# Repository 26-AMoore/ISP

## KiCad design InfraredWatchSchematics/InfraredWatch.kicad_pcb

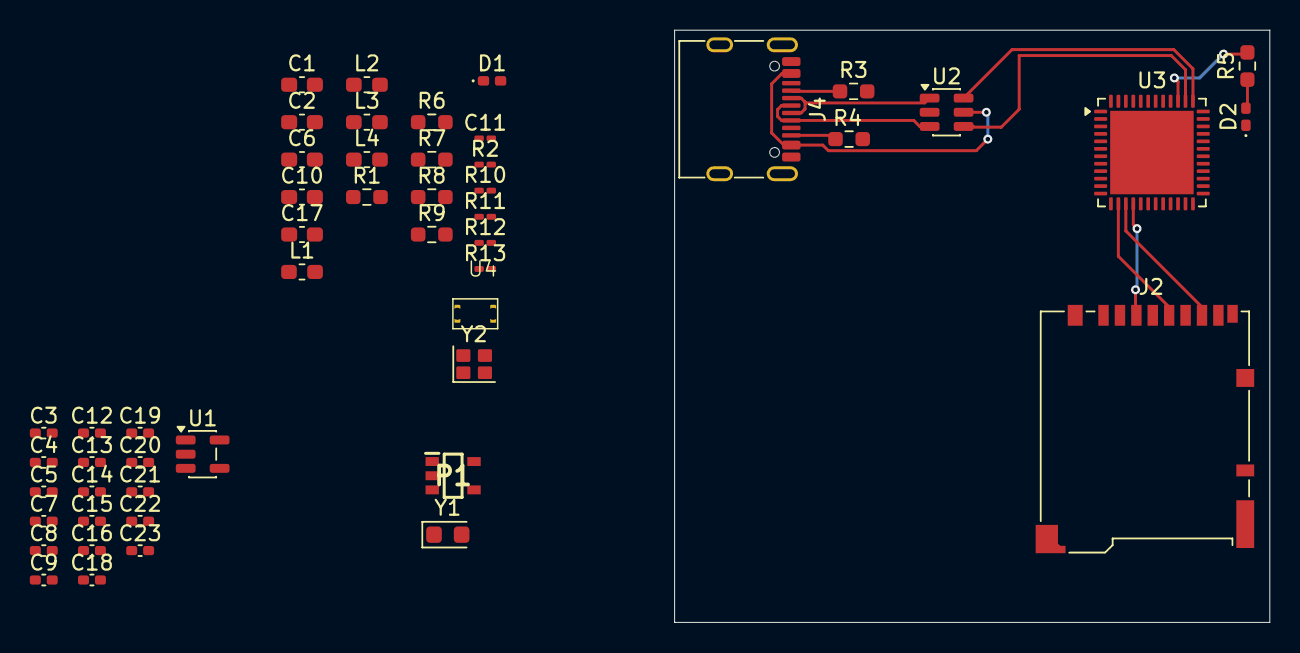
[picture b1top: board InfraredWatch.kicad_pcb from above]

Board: 4 copper layers, 39.9 x 39.7 mm, 51 parts (0 on the bottom side), 32 nets.

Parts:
C1, C2, C6, C10, C17: 4.7uF; C_0603_1608Metric_Pad1.08x0.95mm_HandSolder
C3, C4, C5, C7, C8, C9, C12, C13, C20, C21, C22, C23: 100nF; C_0402_1005Metric_Pad0.74x0.62mm_HandSolder
C11: 10uF; C_0201_0603Metric_Pad0.64x0.40mm_HandSolder
C14: 22uF; C_0402_1005Metric_Pad0.74x0.62mm_HandSolder
C15, C16: C; C_0402_1005Metric_Pad0.74x0.62mm_HandSolder
C18: 0.8pF; C_0402_1005Metric_Pad0.74x0.62mm_HandSolder
C19: 0.3pF; C_0402_1005Metric_Pad0.74x0.62mm_HandSolder
D1: CHARGE_INDICATOR; LED_0402_1005Metric_Pad0.77x0.64mm_HandSolder
D2: LED; LED_0402_1005Metric_Pad0.77x0.64mm_HandSolder
J2: Micro_SD_Card_Det2; microSD_HC_Hirose_DM3BT-DSF-PEJS
J4: USB_C_Receptacle_USB2.0_16P; USB_C_Receptacle_G-Switch_GT-USB-7010ASV
L1, L2: 10uH; L_0603_1608Metric_Pad1.05x0.95mm_HandSolder
L3: 10nH; L_0603_1608Metric_Pad1.05x0.95mm_HandSolder
L4: 2.7nH; L_0603_1608Metric_Pad1.05x0.95mm_HandSolder
P1: XC9265A331MR-G
R1: 2k; R_0603_1608Metric_Pad0.98x0.95mm_HandSolder
R2: 470; R_0201_0603Metric_Pad0.64x0.40mm_HandSolder
R3, R4, R6, R7, R8, R9: 5.1k; R_0603_1608Metric_Pad0.98x0.95mm_HandSolder
R5: R; R_0603_1608Metric_Pad0.98x0.95mm_HandSolder
R10, R11, R12, R13: 100; R_0201_0603Metric_Pad0.64x0.40mm_HandSolder
U1: MCP73831-5-OT; SOT-23-5
U2: USBLC6-2SC6; SOT-23-6
U3: STM32WB55CGU6; QFN-48-1EP_7x7mm_P0.5mm_EP5.6x5.6mm
U4: A1001312
Y1: 32.768kHz; Crystal_SMD_2012-2Pin_2.0x1.2mm_HandSoldering
Y2: 32MHz; Crystal_SMD_SeikoEpson_FA128-4Pin_2.0x1.6mm

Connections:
+BATT: C6.1, C11.1, P1.1 (V_IN), U1.3 (V_{BAT})
/BOOT0/Button3: C23.1, R9.1, R13.1, U3.4 (PH3)
/HSC_In: U3.25 (OSC_IN), Y2.1
/HSC_Out: U3.24 (OSC_OUT), Y2.3
/IR: R5.2, U3.39 (PA13)
/LSE_In: C16.1, U3.2 (PC14), Y1.2
/LSE_Out: C15.1, U3.3 (PC15), Y1.1
/RF: C18.1, L4.1, U3.21 (RF1)
/SD_CLK: J2.5 (CLK), U3.14 (PA5)
/SD_MISO: J2.7 (DAT0), U3.15 (PA6)
/SD_MOSI: J2.3 (CMD), U3.16 (PA7)
/SMBSFB: C17.2, L3.2, U3.31 (VFBSMPS)
/SMBSLX: L2.1, U3.33 (VLXSMPS)
/USB_D+: U2.4 (I/O2), U3.38 (PA12)
/USB_D-: U2.6 (I/O1), U3.37 (PA11)
Button0: C20.1, R6.1, R10.1, U3.9 (PA0)
Button1: C21.1, R7.1, R11.1, U3.10 (PA1)
Button2: C22.1, R8.1, R12.1, U3.11 (PA2)
CHARGE_IN: C1.1, J4.A4 (VBUS), J4.A9 (VBUS), J4.B4 (VBUS), J4.B9 (VBUS), R2.1, U1.4 (V_{DD}), U2.5 (VBUS)
GND: C1.2, C2.2, C3.2, C4.2, C5.2, C6.2, C7.2, C8.2, C9.2, C10.2, C11.2, C12.2, C13.2, C14.2, C15.2, C16.2, C17.1, C18.2, C19.2, C20.2, C21.2, C22.2, C23.2, D2.1 (K), J2.2 (DAT3/CD), J2.6 (VSS), J4.A1 (GND), J4.A12 (GND), J4.B1 (GND), J4.B12 (GND), J4.SH (SHIELD), P1.2 (GND), R1.1, R3.2, R4.2, R6.2, R7.2, R8.2, R9.2, U1.2 (V_{SS}), U2.2 (GND), U3.22 (VSSRF), U3.32 (VSSSMPS), U3.49 (VSS), U4.2 (GND), Y2.2 (G), Y2.4 (G)
unnamed: D1.2 (A), R2.2
unnamed: D1.1 (K), U1.1 (STAT)
unnamed: D2.2 (A), R5.1
unnamed: C19.1, L4.2
unnamed: J4.A5 (CC1), R3.1
unnamed: J4.B5 (CC2), R4.1
unnamed: J4.A6 (D+), J4.B6 (D+), U2.3 (I/O2)
unnamed: J4.A7 (D-), J4.B7 (D-), U2.1 (I/O1)
unnamed: L2.2, L3.1
unnamed: L1.1, P1.5 (LX)
unnamed: R1.2, U1.5 (PROG)
Power: C2.1, C3.1, C4.1, C5.1, C7.1, C8.1, C9.1, C10.1, C12.1, C13.1, C14.1, J2.4 (VDD), L1.2, P1.4 (V_OUT), U3.1 (VBAT), U3.8 (VDDA), U3.20 (VDD), U3.23 (VDDRF), U3.34 (VDDSMPS), U3.35 (VDD), U3.40 (VDDUSB), U3.48 (VDD)

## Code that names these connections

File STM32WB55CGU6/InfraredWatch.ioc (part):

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Mcu.Name=STM32WB55CCUx
Mcu.Package=UFQFPN48
Mcu.UserName=STM32WB55CCUx
PA0.Signal=GPIO_Input
PA1.Signal=GPIO_Input
PA11.Mode=Device
PA11.Signal=USB_DM
PA12.Mode=Device
PA12.Signal=USB_DP
PA13.Signal=IR_OUT
PA2.Signal=GPIO_Input
PA5.Mode=Full_Duplex_Master
PA5.Signal=SPI1_SCK
PA6.Mode=Full_Duplex_Master
PA6.Signal=SPI1_MISO
PA7.Mode=Full_Duplex_Master
PA7.Signal=SPI1_MOSI
PB6.Mode=Asynchronous
PB6.Signal=USART1_TX
PB7.Mode=Asynchronous
PB7.Signal=USART1_RX
PC14-OSC32_IN.Mode=LSE-External-Oscillator
PC14-OSC32_IN.Signal=RCC_OSC32_IN
PC15-OSC32_OUT.Mode=LSE-External-Oscillator
PC15-OSC32_OUT.Signal=RCC_OSC32_OUT
RCC.HSE_VALUE=32000000
RCC.SYSCLKFreq_VALUE=64000000
RCC.SYSCLKSource=RCC_SYSCLKSOURCE_PLLCLK
board=custom

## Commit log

2026-03-27 init
2026-03-27 made ignore marginally prettier
2026-03-27 update kicad and add chip layout
2026-03-27 pressed the generate code button
2026-03-28 pcb updates, added first watch idea
2026-03-28 Fri Mar 27 23:28:05 EDT 2026
2026-03-29 Sat Mar 28 22:20:19 EDT 2026
2026-03-29 added progress.md
2026-03-29 Sun Mar 29 09:52:52 EDT 2026 added SMD ble chip
2026-04-02 Thu Apr 2 09:39:45 EDT 2026 | updated pcb
2026-04-29 Wed Apr 29 09:42:28 EDT 2026 | updated pcb
